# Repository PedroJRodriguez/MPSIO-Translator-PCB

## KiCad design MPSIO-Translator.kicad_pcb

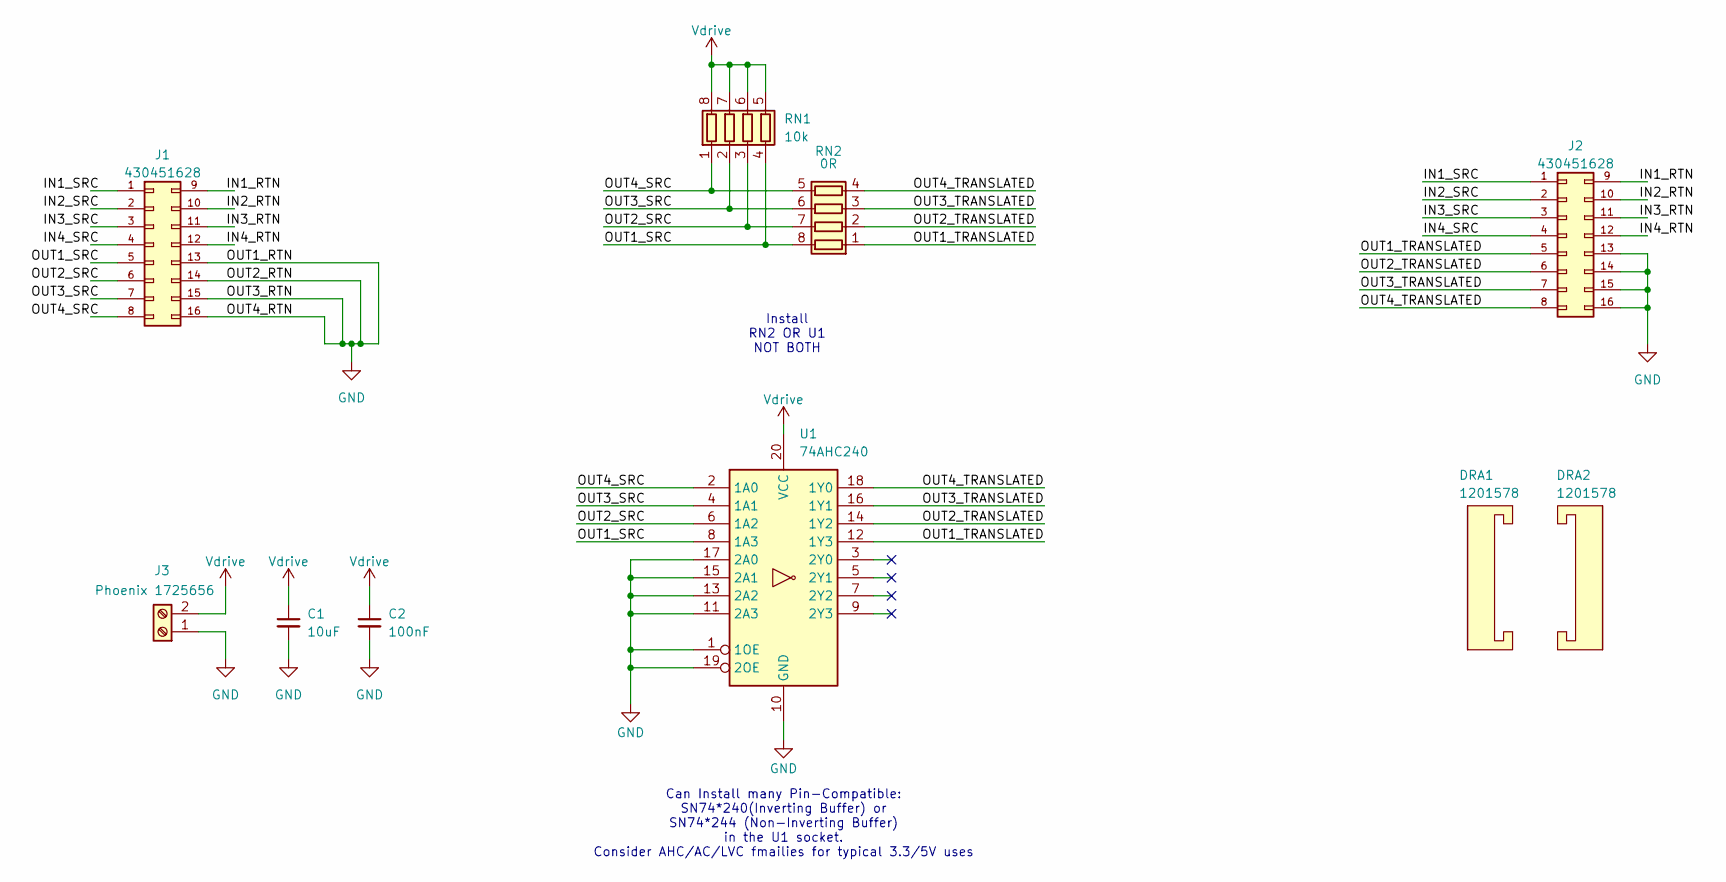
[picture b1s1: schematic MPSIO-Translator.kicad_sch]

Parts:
C1: 10uF; C_0805_2012Metric_Pad1.18x1.45mm_HandSolder; Manufacture Part Number GRM21BR61H106KE43L
C2: 100nF; C_0805_2012Metric_Pad1.18x1.45mm_HandSolder; Manufacture Part Number KGM21NR71H104KT
DRA1, DRA2: 1201578; DINRailAdapter_3xM3_PhoenixContact_1201578; Manufacture Part Number 1201578
J1, J2: 430451628; Manufacture Part Number 0430451628
J3: Phoenix 1725656; TerminalBlock_Phoenix_MPT-0,5-2-2.54_1x02_P2.54mm_Horizontal; Manufacture Part Number 1725656
RN1: 10k; R_Array_Convex_4x1206; Manufacture Part Number EXB-38V103JV
RN2: 0R; R_Array_Convex_4x1206; Manufacture Part Number YC164-JR-130RL
U1: 74AHC240; DIP-20_W7.62mm_Socket_LongPads; Manufacture Part Number 2485264-6

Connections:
/IN1_RTN: J1.9, J2.9
/IN1_SRC: J1.1, J2.1
/IN2_RTN: J1.10, J2.10
/IN2_SRC: J1.2, J2.2
/IN3_RTN: J1.11, J2.11
/IN3_SRC: J1.3, J2.3
/IN4_RTN: J1.12, J2.12
/IN4_SRC: J1.4, J2.4
/OUT1_SRC: J1.5, RN1.4 (R4.1), RN2.8 (R1.2), U1.8 (1A3)
/OUT1_TRANSLATED: J2.5, RN2.1 (R1.1), U1.12 (1Y3)
/OUT2_SRC: J1.6, RN1.3 (R3.1), RN2.7 (R2.2), U1.6 (1A2)
/OUT2_TRANSLATED: J2.6, RN2.2 (R2.1), U1.14 (1Y2)
/OUT3_SRC: J1.7, RN1.2 (R2.1), RN2.6 (R3.2), U1.4 (1A1)
/OUT3_TRANSLATED: J2.7, RN2.3 (R3.1), U1.16 (1Y1)
/OUT4_SRC: J1.8, RN1.1 (R1.1), RN2.5 (R4.2), U1.2 (1A0)
/OUT4_TRANSLATED: J2.8, RN2.4 (R4.1), U1.18 (1Y0)
GND: C1.2, C2.2, J1.13, J1.14, J1.15, J1.16, J2.13, J2.14, J2.15, J2.16, J3.1, U1.1 (1OE), U1.10 (GND), U1.11 (2A3), U1.13 (2A2), U1.15 (2A1), U1.17 (2A0), U1.19 (2OE)
Vdrive: C1.1, C2.1, J3.2, RN1.5 (R4.2), RN1.6 (R3.2), RN1.7 (R2.2), RN1.8 (R1.2), U1.20 (VCC)

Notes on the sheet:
Can Install many Pin-Compatible: SN74*240(Inverting Buffer) or SN74*244 (Non-Inverting Buffer) in the U1 socket. Consider AHC/AC/LVC fmailies for typical 3.3/5V uses
Install RN2 OR U1 NOT BOTH

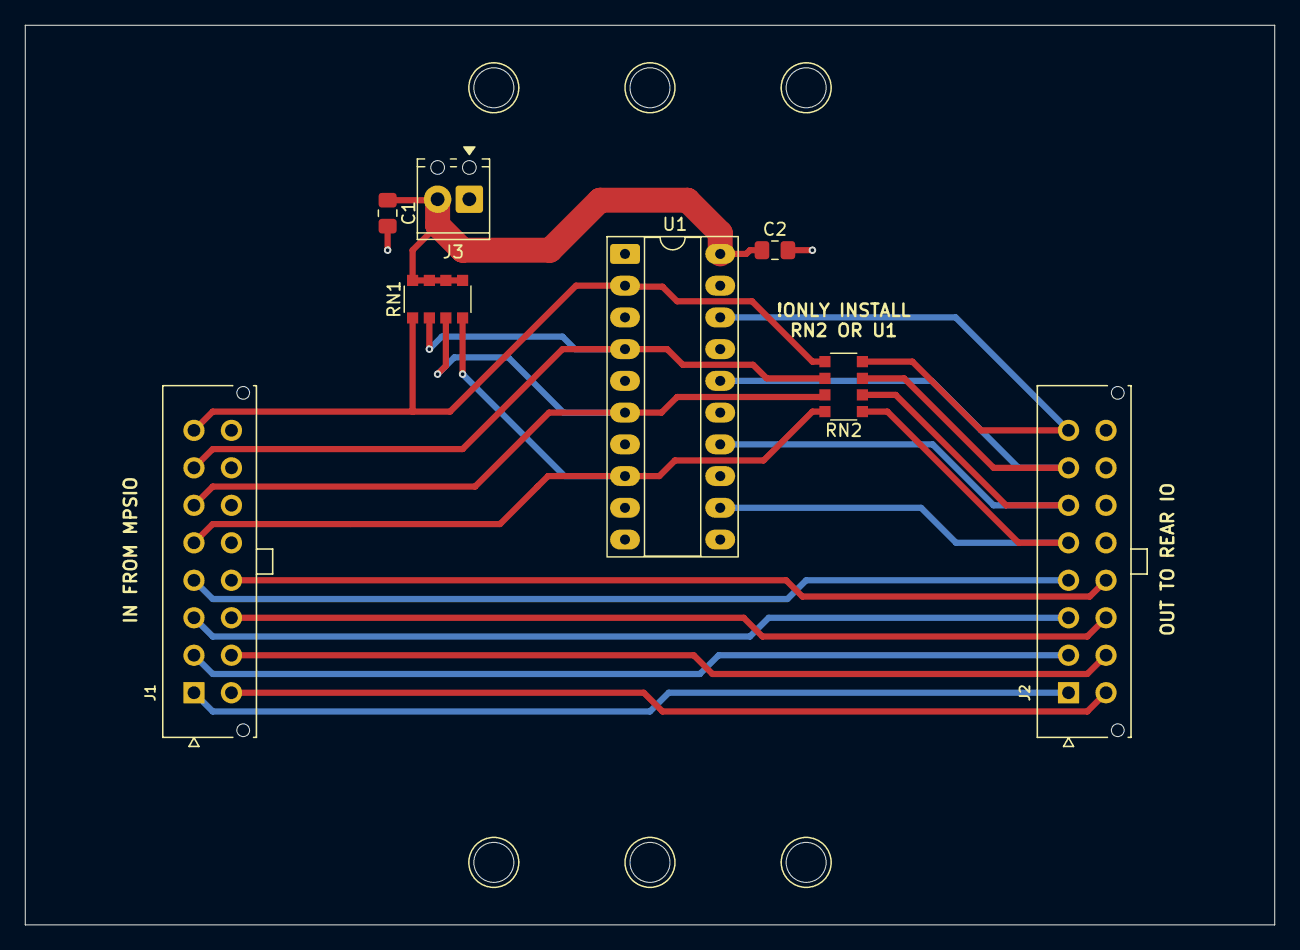
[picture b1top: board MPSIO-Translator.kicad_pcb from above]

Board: 2 copper layers, 100.0 x 72.0 mm, 10 parts (0 on the bottom side), 18 nets.

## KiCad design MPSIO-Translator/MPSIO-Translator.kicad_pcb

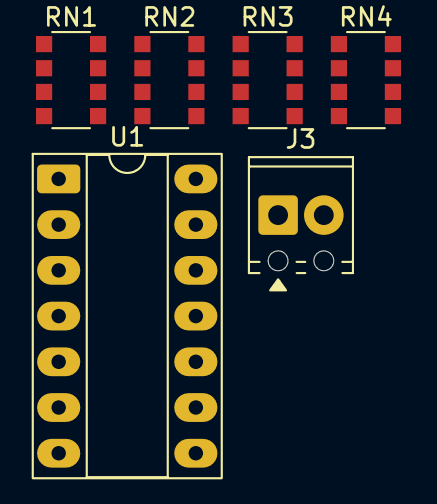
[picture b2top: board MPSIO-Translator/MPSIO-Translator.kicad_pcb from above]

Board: 2 copper layers, 6 parts (0 on the bottom side), 6 nets, no tracks yet.

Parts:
J3: Screw_Terminal_01x02; TerminalBlock_Phoenix_MPT-0,5-2-2.54_1x02_P2.54mm_Horizontal
RN1, RN3, RN4: 0R; R_Array_Convex_4x1206
RN2: 10k; R_Array_Convex_4x1206
U1: 74LS125; DIP-14_W7.62mm_Socket_LongPads

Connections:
/OUT1_SRC: RN2.1 (R1.1), RN3.5 (R4.2), RN4.5 (R4.2)
/OUT2_SRC: RN2.2 (R2.1), RN3.6 (R3.2), RN4.6 (R3.2)
/OUT3_SRC: RN2.3 (R3.1), RN3.7 (R2.2), RN4.7 (R2.2)
/OUT4_SRC: RN2.4 (R4.1), RN3.8 (R1.2), RN4.8 (R1.2)
GND: J3.1, RN1.1 (R1.1), RN1.2 (R2.1), RN1.3 (R3.1), RN1.4 (R4.1)
Vdrive: J3.2, RN2.5 (R4.2), RN2.6 (R3.2), RN2.7 (R2.2), RN2.8 (R1.2)

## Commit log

2025-09-12 Inital Commit of Basic Schematic
2025-09-17 Completed Draft of Design
    Initial Draft
